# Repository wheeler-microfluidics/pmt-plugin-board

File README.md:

# pmt-plugin-board
Kicad files based on mr-box-peripheral-board (http://microfluidics.utoronto.ca/gitlab/gcc-project/mr-box-peripheral-board.kicad)
to be used with pmt-plugin (https://github.com/wheeler-microfluidics/pmt-plugin).

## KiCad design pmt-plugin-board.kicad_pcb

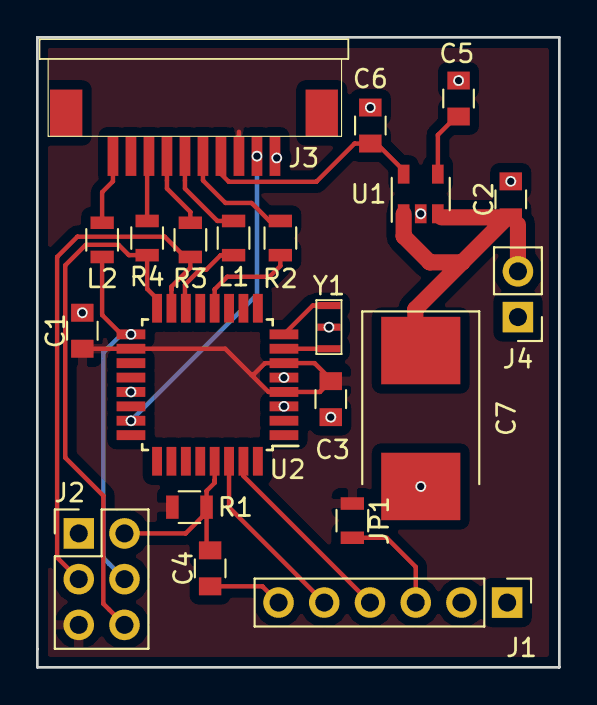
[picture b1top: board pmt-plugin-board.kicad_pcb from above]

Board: 2 copper layers, 29.0 x 35.0 mm, 21 parts (0 on the bottom side), 23 nets.

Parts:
C1, C3, C4: 0.1uF; C_0805
C2: 1uF; C_0805
C5: 100pF; C_0805
C6: 2.2uF; C_0805
C7: 100uF; CP_Tantalum_Case-E_EIA-7260-38_Hand
J1: CONN_ARDUINO; Pin_Header_Straight_1x06_Pitch2.54mm
J2: CONN_ISP; Pin_Header_Straight_2x03_Pitch2.54mm
J3: PMT Connector; CONN-FPC-B-RA-10POS-1mm
J4: 12V In; Pin_Header_Straight_1x02_Pitch2.54mm
JP1: 3.3V-3.3V_USB; R_0805
L1, L2: FB; L_0805
R1: 10k; R_0805
R2, R3, R4: 50; R_0805
U1: 5V Regulator; SOT-23-5
U2: ATMEGA328P-AU; TQFP-32_7x7mm_Pitch0.8mm
Y1: Resonator; CSTCE_G15C

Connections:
+3.3V: C1.1, C3.1, J2.5, J3.3, JP1.2, R1.2, U2.4, U2.6, U2.18
+3.3V_USB: J1.3, JP1.1
+5V: C6.1, J3.4, U1.5
+12V: C2.1, C7.1, J4.2, U1.1, U1.3
CS_ADC: R3.1, U2.14
CS_POT: R2.2, U2.12
GND: C1.2, C2.2, C3.2, C5.2, C6.2, C7.2, J1.1, J2.1, J3.1, J4.1, U1.2, U2.3, U2.5, U2.21, Y1.2
MISO: J2.6, R4.1, U2.16
MONITOR: J3.2, U2.23
MOSI: J2.3, L1.2, U2.15
unnamed: C4.1, J1.6
unnamed: C5.1, U1.4
unnamed: J3.5, R2.1
unnamed: J3.6, R3.2
unnamed: J3.7, L1.1
unnamed: J3.8, R4.2
unnamed: J3.10, L2.2
unnamed: U2.7, Y1.3
unnamed: U2.8, Y1.1
RST: C4.2, J2.2, R1.1, U2.29
RX: J1.5, U2.30
SCK: J2.4, L2.1, U2.17
TX: J1.4, U2.31

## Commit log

2017-12-07 Add gerber files
2017-12-11 Add gitmodules
2017-12-11 Redirect library to git repository
2017-12-11 remove .gitmodules
2017-12-11 add gitmodules file to point to github library
2017-12-11 fix gitmodules
2017-12-11 add .gitattributes
